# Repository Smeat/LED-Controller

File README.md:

# LED-Controller
Control multiple LED-strips (or other things) using a nrf24l01 or esp8266

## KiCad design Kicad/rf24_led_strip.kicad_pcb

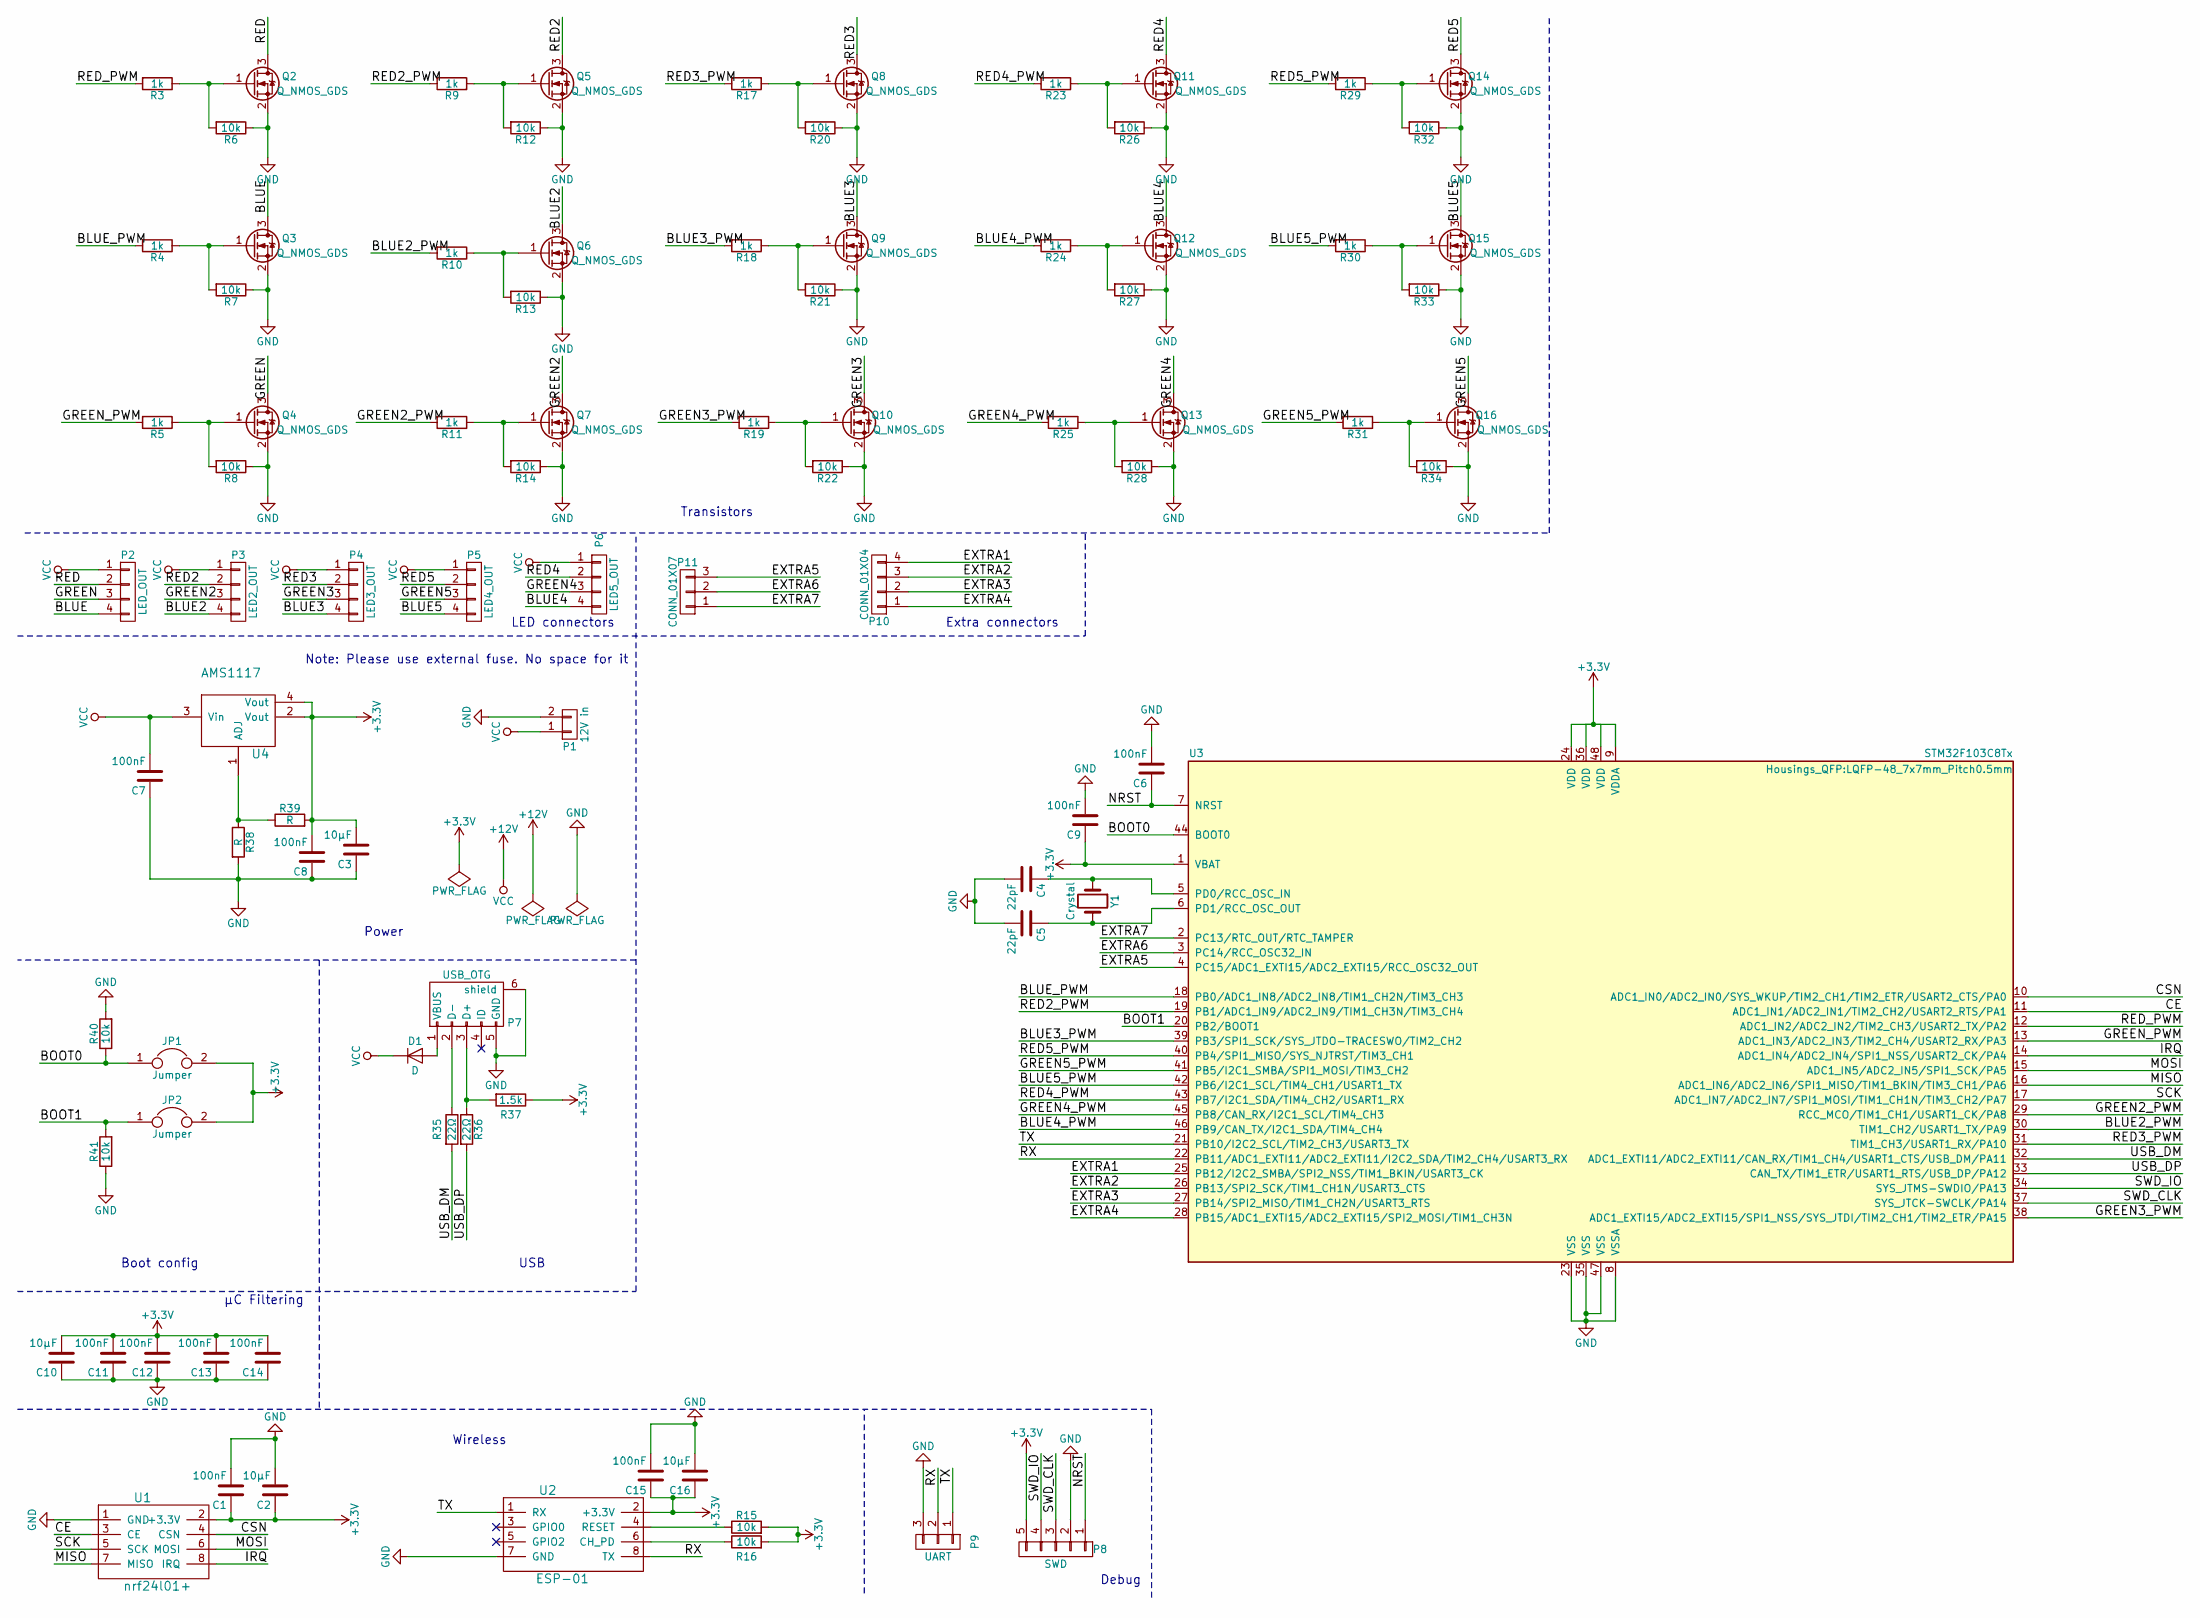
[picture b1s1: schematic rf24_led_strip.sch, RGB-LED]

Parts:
C1, C6, C7, C8, C9, C11, C12, C13, C14, C15: 100nF; C_0603_HandSoldering
C2, C3, C10, C16: 10µF; C_0805
C4, C5: 22pF; C_Disc_D3.0mm_W2.0mm_P2.50mm
D1: D; D_SOD-123
JP1, JP2: Jumper; Pin_Header_Straight_1x02_Pitch2.54mm
P1: 12V in; TerminalBlock_Pheonix_MKDS1.5-2pol
P2: LED_OUT; Pin_Header_Straight_1x04_Pitch2.54mm
P3: LED2_OUT; Pin_Header_Straight_1x04_Pitch2.54mm
P4: LED3_OUT; Pin_Header_Straight_1x04_Pitch2.54mm
P5: LED4_OUT; Pin_Header_Straight_1x04_Pitch2.54mm
P6: LED5_OUT; Pin_Header_Straight_1x04_Pitch2.54mm
P7: USB_OTG; USB_Micro-B_Molex_47346-0001
P8: SWD; Pin_Header_Straight_1x05_Pitch2.54mm
P9: UART; Pin_Header_Straight_1x03_Pitch2.54mm
P10: CONN_01X04; Pin_Header_Straight_1x04_Pitch2.54mm
P11: CONN_01X07; Pin_Header_Straight_1x03_Pitch2.54mm
Q2, Q3, Q4, Q5, Q6, Q7, Q8, Q9, Q10, Q11, Q12, Q13, Q14, Q15, Q16: Q_NMOS_GDS; SOT-23
R3, R4, R5, R9, R10, R11, R17, R18, R19, R23, R24, R25, R29, R30, R31: 1k; R_0805
R6, R7, R8, R12, R13, R14, R15, R16, R20, R21, R22, R26, R27, R28, R32, R33, R34, R40, R41: 10k; R_0805
R35, R36: 22Ω; R_0805
R37: 1.5k; R_0805
R38, R39: R; R_0805
U1: nrf24l01+; Pin_Header_Straight_2x04_Pitch2.54mm
U2: ESP-01; Pin_Header_Straight_2x04_Pitch2.54mm
U3: STM32F103C8Tx; LQFP-48_7x7mm_Pitch0.5mm
U4: AMS1117; SOT-223
Y1: Crystal; Crystal_HC49-4H_Vertical

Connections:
+3V3: C1.1, C2.1, C3.2, C8.2, C9.1, C10.2, C11.2, C12.2, C13.2, C14.2, C15.1, C16.1, JP1.2, JP2.2, P8.5, R15.2, R16.2, R37.1, R39.2, U1.2 (+3.3V), U2.2 (+3.3V), U3.1 (VBAT), U3.9 (VDDA), U3.24 (VDD), U3.36 (VDD), U3.48 (VDD), U4.2 (Vout), U4.4 (Vout)
+12V: C7.2, D1.1 (K), P1.1, P2.1, P3.1, P4.1, P5.1, P6.1, U4.3 (Vin)
/BLUE: P2.4, Q3.3 (D)
/BLUE2: P3.4, Q6.3 (D)
/BLUE2_PWM: R10.2, U3.30 (TIM1_CH2/USART1_TX/PA9)
/BLUE3: P4.4, Q9.3 (D)
/BLUE3_PWM: R18.2, U3.39 (PB3/SPI1_SCK/SYS_JTDO-TRACESWO/TIM2_CH2)
/BLUE4: P6.4, Q12.3 (D)
/BLUE4_PWM: R24.2, U3.46 (PB9/CAN_TX/I2C1_SDA/TIM4_CH4)
/BLUE5: P5.4, Q15.3 (D)
/BLUE5_PWM: R30.2, U3.42 (PB6/I2C1_SCL/TIM4_CH1/USART1_TX)
/BLUE_PWM: R4.2, U3.18 (PB0/ADC1_IN8/ADC2_IN8/TIM1_CH2N/TIM3_CH3)
/BOOT0: JP1.1, R40.1, U3.44 (BOOT0)
/BOOT1: JP2.1, R41.2, U3.20 (PB2/BOOT1)
/CE: U1.3 (CE), U3.11 (ADC1_IN1/ADC2_IN1/TIM2_CH2/USART2_RTS/P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)
/CSN: U1.4 (CSN), U3.10 (ADC1_IN0/ADC2_IN0/SYS_WKUP/TIM2_CH1/TIM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)
/EXTRA1: P10.4, U3.25 (PB12/I2C2_SMBA/SPI2_NSS/TIM1_BKIN/USART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)
/EXTRA2: P10.3, U3.26 (PB13/SPI2_SCK/TIM1_CH1N/USART3_CTS)
/EXTRA3: P10.2, U3.27 (PB14/SPI2_MISO/TIM1_CH2N/USART3_RTS)
/EXTRA4: P10.1, U3.28 (PB15/ADC1_EXTI15/ADC2_EXTI15/SPI2_MOSI/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)
/EXTRA5: P11.3, U3.4 (PC15/ADC1_EXTI15/ADC2_EXTI15/RCC_OSC32_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)
/EXTRA6: P11.2, U3.3 (PC14/RCC_OSC32_IN)
/EXTRA7: P11.1, U3.2 (PC13/RTC_OUT/RTC_TAMPER)
/GREEN: P2.3, Q4.3 (D)
/GREEN2: P3.3, Q7.3 (D)
/GREEN2_PWM: R11.2, U3.29 (RCC_MCO/TIM1_CH1/USART1_CK/PA8)
/GREEN3: P4.3, Q10.3 (D)
/GREEN3_PWM: R19.2, U3.38 (ADC1_EXTI15/ADC2_EXTI15/SPI1_NSS/SYS_JT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)
/GREEN4: P6.3, Q13.3 (D)
/GREEN4_PWM: R25.2, U3.45 (PB8/CAN_RX/I2C1_SCL/TIM4_CH3)
/GREEN5: P5.3, Q16.3 (D)
/GREEN5_PWM: R31.2, U3.41 (PB5/I2C1_SMBA/SPI1_MOSI/TIM3_CH2)
/GREEN_PWM: R5.2, U3.13 (ADC1_IN3/ADC2_IN3/TIM2_CH4/USART2_RX/PA3)
/IRQ: U1.8 (IRQ), U3.14 (ADC1_IN4/ADC2_IN4/SPI1_NSS/USART2_CK/PA4)
/MISO: U1.7 (MISO), U3.16 (ADC1_IN6/ADC2_IN6/SPI1_MISO/TIM1_BKIN/T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)
/MOSI: U1.6 (MOSI), U3.15 (ADC1_IN5/ADC2_IN5/SPI1_SCK/PA5)
/NRST: C6.1, P8.1, U3.7 (NRST)
/RED: P2.2, Q2.3 (D)
/RED2: P3.2, Q5.3 (D)
/RED2_PWM: R9.2, U3.19 (PB1/ADC1_IN9/ADC2_IN9/TIM1_CH3N/TIM3_CH4)
/RED3: P4.2, Q8.3 (D)
/RED3_PWM: R17.2, U3.31 (TIM1_CH3/USART1_RX/PA10)
/RED4: P6.2, Q11.3 (D)
/RED4_PWM: R23.2, U3.43 (PB7/I2C1_SDA/TIM4_CH2/USART1_RX)
/RED5: P5.2, Q14.3 (D)
/RED5_PWM: R29.2, U3.40 (PB4/SPI1_MISO/SYS_NJTRST/TIM3_CH1)
/RED_PWM: R3.2, U3.12 (ADC1_IN2/ADC2_IN2/TIM2_CH3/USART2_TX/PA2)
/RX: P9.2, U2.8 (TX), U3.22 (PB11/ADC1_EXTI11/ADC2_EXTI11/I2C2_SDA/T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)
/SCK: U1.5 (SCK), U3.17 (ADC1_IN7/ADC2_IN7/SPI1_MOSI/TIM1_CH1N/T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)
/SWD_CLK: P8.3, U3.37 (SYS_JTCK-SWCLK/PA14)
/SWD_IO: P8.4, U3.34 (SYS_JTMS-SWDIO/PA13)
/TX: P9.1, U2.1 (RX), U3.21 (PB10/I2C2_SCL/TIM2_CH3/USART3_TX)
/USB_DM: R35.2, U3.32 (ADC1_EXTI11/ADC2_EXTI11/CAN_RX/TIM1_CH4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)
/USB_DP: R36.2, U3.33 (CAN_TX/TIM1_ETR/USART1_RTS/USB_DP/PA12)
GND: C1.2, C2.2, C3.1, C4.2, C5.2, C6.2, C7.1, C8.1, C9.2, C10.1, C11.1, C12.1, C13.1, C14.1, C15.2, C16.2, P1.2, P7.5 (GND), P7.6 (shield), P8.2, P9.3, Q2.2 (S), Q3.2 (S), Q4.2 (S), Q5.2 (S), Q6.2 (S), Q7.2 (S), Q8.2 (S), Q9.2 (S), Q10.2 (S), Q11.2 (S), Q12.2 (S), Q13.2 (S), Q14.2 (S), Q15.2 (S), Q16.2 (S), R6.1, R7.1, R8.1, R12.1, R13.1, R14.1, R20.1, R21.1, R22.1, R26.1, R27.1, R28.1, R32.1, R33.1, R34.1, R38.2, R40.2, R41.1, U1.1 (GND), U2.7 (GND), U3.8 (VSSA), U3.23 (VSS), U3.35 (VSS), U3.47 (VSS)
unnamed: C4.1, U3.5 (PD0/RCC_OSC_IN), Y1.1
unnamed: C5.1, U3.6 (PD1/RCC_OSC_OUT), Y1.2
unnamed: D1.2 (A), P7.1 (VBUS)
unnamed: P7.2 (D-), R35.1
unnamed: P7.3 (D+), R36.1, R37.2
unnamed: Q2.1 (G), R3.1, R6.2
unnamed: Q3.1 (G), R4.1, R7.2
unnamed: Q4.1 (G), R5.1, R8.2
unnamed: Q5.1 (G), R9.1, R12.2
unnamed: Q6.1 (G), R10.1, R13.2
unnamed: Q7.1 (G), R11.1, R14.2
unnamed: Q8.1 (G), R17.1, R20.2
unnamed: Q9.1 (G), R18.1, R21.2
unnamed: Q10.1 (G), R19.1, R22.2
unnamed: Q11.1 (G), R23.1, R26.2
unnamed: Q12.1 (G), R24.1, R27.2
unnamed: Q13.1 (G), R25.1, R28.2
unnamed: Q14.1 (G), R29.1, R32.2
unnamed: Q15.1 (G), R30.1, R33.2
unnamed: Q16.1 (G), R31.1, R34.2
unnamed: R15.1, U2.4 (RESET)
unnamed: R16.1, U2.6 (CH_PD)
unnamed: R38.1, R39.1, U4.1 (ADJ)

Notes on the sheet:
Wireless
Transistors
LED connectors
Power
Extra connectors
Boot config
USB
µC Filtering
Debug
Note: Please use external fuse. No space for it

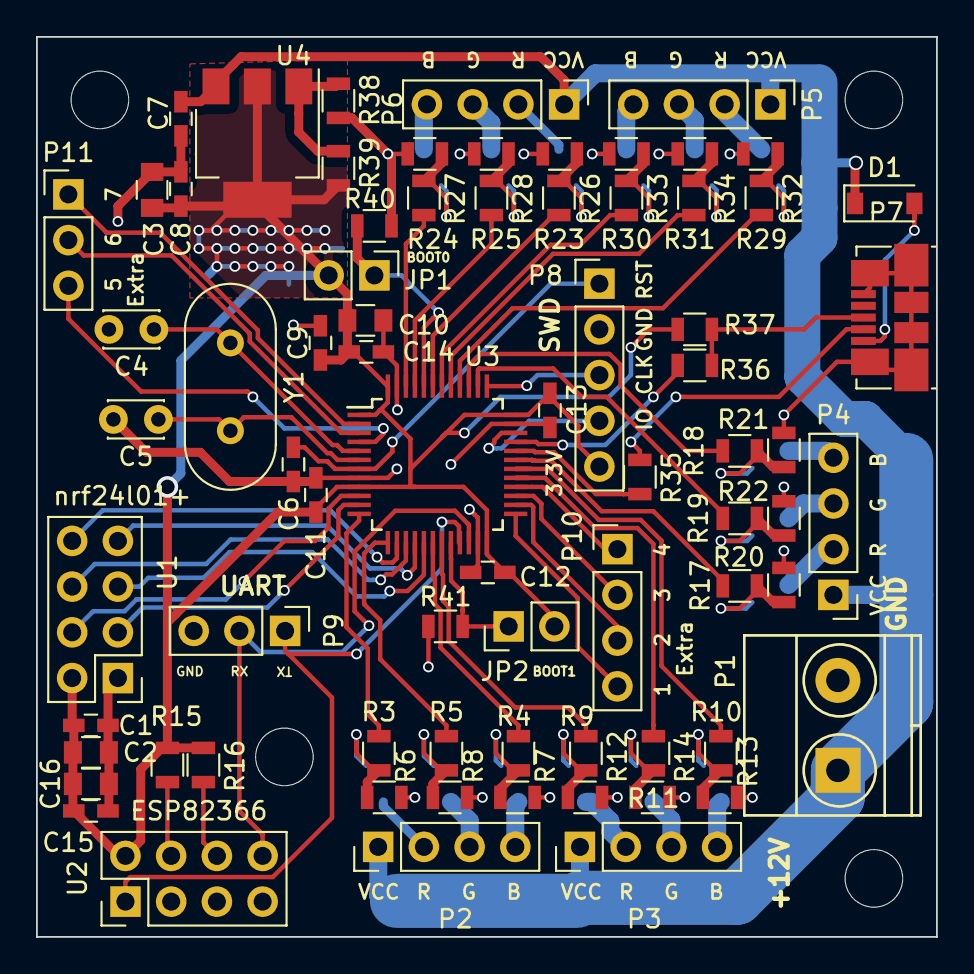
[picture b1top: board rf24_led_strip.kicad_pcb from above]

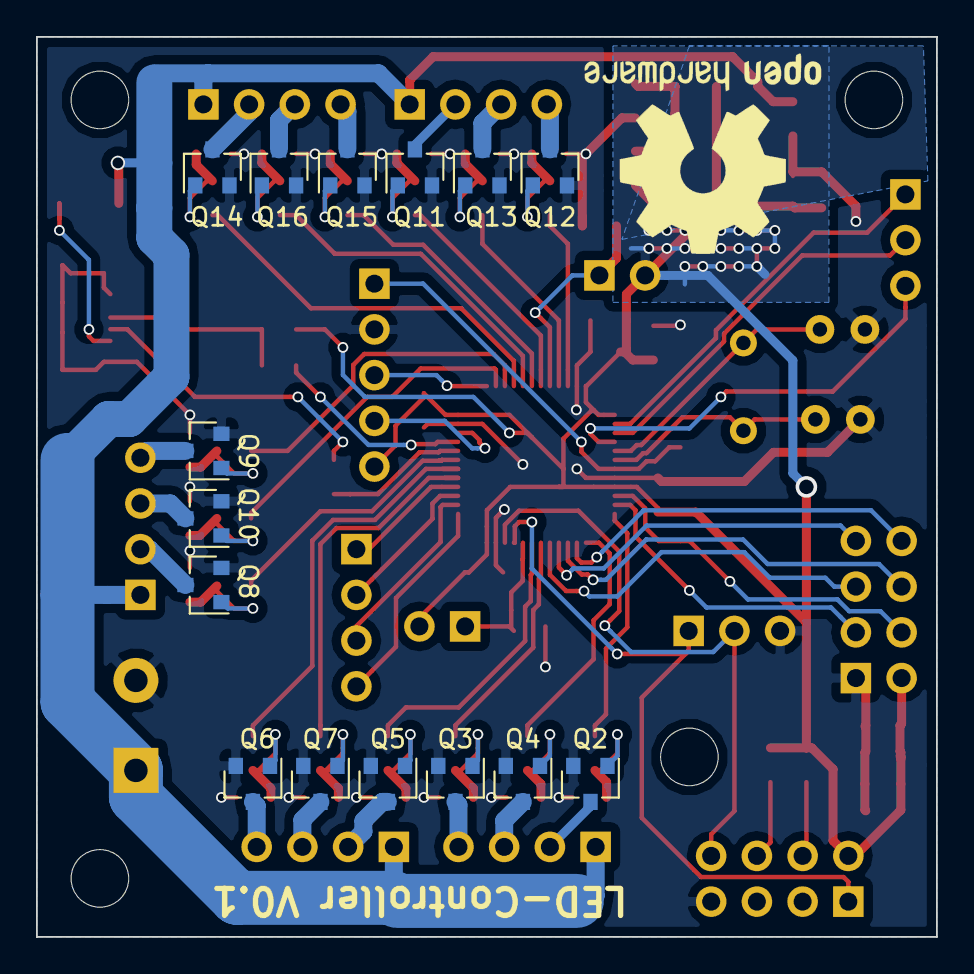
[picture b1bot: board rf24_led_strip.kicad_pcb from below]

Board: 2 copper layers, 50.0 x 50.0 mm, 89 parts (15 on the bottom side), 78 nets.

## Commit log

2017-03-23 3.3V Version.
2017-03-23 First commit.
2017-03-23 STM32 schematic done.
2017-03-23 First pcb version.
2017-03-23 First "complete" stm32 version.
2017-03-23 Remove net file.
2017-03-23 Fix wireless connectors.
2017-03-23 Fix micro usb.
2017-03-23 Add gitattributes.
2017-03-24 Fix spacing for ESP8266.
2017-03-24 Update power supply.
2017-03-24 Add capacitors to the ESP8266.
2017-03-24 Update pictures.
